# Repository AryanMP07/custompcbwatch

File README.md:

# Custom PCB Smartwatch

A self-contained smartwatch built around an ESP32 microcontroller and a round color display — a first custom PCB project, scoped to be finishable by a beginner and demoable as a resume/portfolio piece.

## Status

- [ ] Breadboard prototype validated
- [ ] Schematic complete (KiCad)
- [ ] ERC clean
- [ ] PCB layout complete
- [ ] DRC clean
- [ ] Gerbers exported
- [ ] PCB ordered
- [ ] Components ordered
- [ ] Board assembled
- [ ] Power-on / bring-up passed
- [ ] Firmware complete

*(Update this checklist as the project progresses.)*

## Core features

- ESP32-WROOM-32 — WiFi, NTP time sync, runs the firmware
- GC9A01 1.28" round SPI display, 240x240 — analog watch face with drawn hands/ticks
- Weather via Open-Meteo, refreshed periodically, with icons
- Single button to cycle screens: time / weather / date / extra info
- LDR-based auto-dim at night
- Battery percentage via a voltage-divider on one ADC pin
- WS2812 ("NeoPixel") RGB status LED — notifications / charging / low battery
- Coin vibration motor (single NPN transistor + flyback diode) for alerts
- MCP73831 LiPo charger IC + USB-C power input

## Repo structure

- KiCad project files (schematic, PCB, footprints, libraries) live at the repo root.
- `.gitignore` excludes KiCad backup/cache/autosave files, netlists, and exported BOM files — see that file for the full list.

## Collaboration workflow

KiCad's `.kicad_sch` / `.kicad_pcb` files don't diff or merge cleanly like code, so two people editing the same file at once causes painful conflicts. Rule of thumb:

1. `git pull` before opening KiCad.
2. Let the other person know you're working on the schematic/PCB.
3. Close KiCad, then `git add -A && git commit -m "..." && git push`.
4. Tell the other person when you're done so they can pull.

## Bill of materials (summary)

ESP32-WROOM-32 · GC9A01 240x240 round SPI display · MCP73831T-2ACI/OT LiPo charger · USB-C power-only connector · 3.7V 500mAh LiPo (JST-PH, protected) · SMD tactile button · LDR + divider resistor · WS2812 RGB LED · coin vibration motor + NPN transistor + flyback diode + base resistor · AMS1117-3.3 regulator (if needed) · 0603/0805 resistor & capacitor kits · programming header.

## Build sequence

1. Learn the basics (voltage/current, resistors/capacitors, SPI/I2C).
2. Breadboard prototype using dev boards (ESP32 dev board + GC9A01 breakout) to validate the concept.
3. KiCad: schematic → ERC → footprints/layout → DRC → Gerbers.
4. Order the bare PCB and all components (matching footprints exactly).
5. Solder the board; verify voltages with a multimeter before connecting the battery.
6. Bring up subsystems one at a time: LED blink → display → WiFi → vibration motor.
7. Write and flash firmware: WiFi + NTP → weather API → watch-face rendering → button screen-cycling → auto-dim → RGB LED status → vibration alerts.

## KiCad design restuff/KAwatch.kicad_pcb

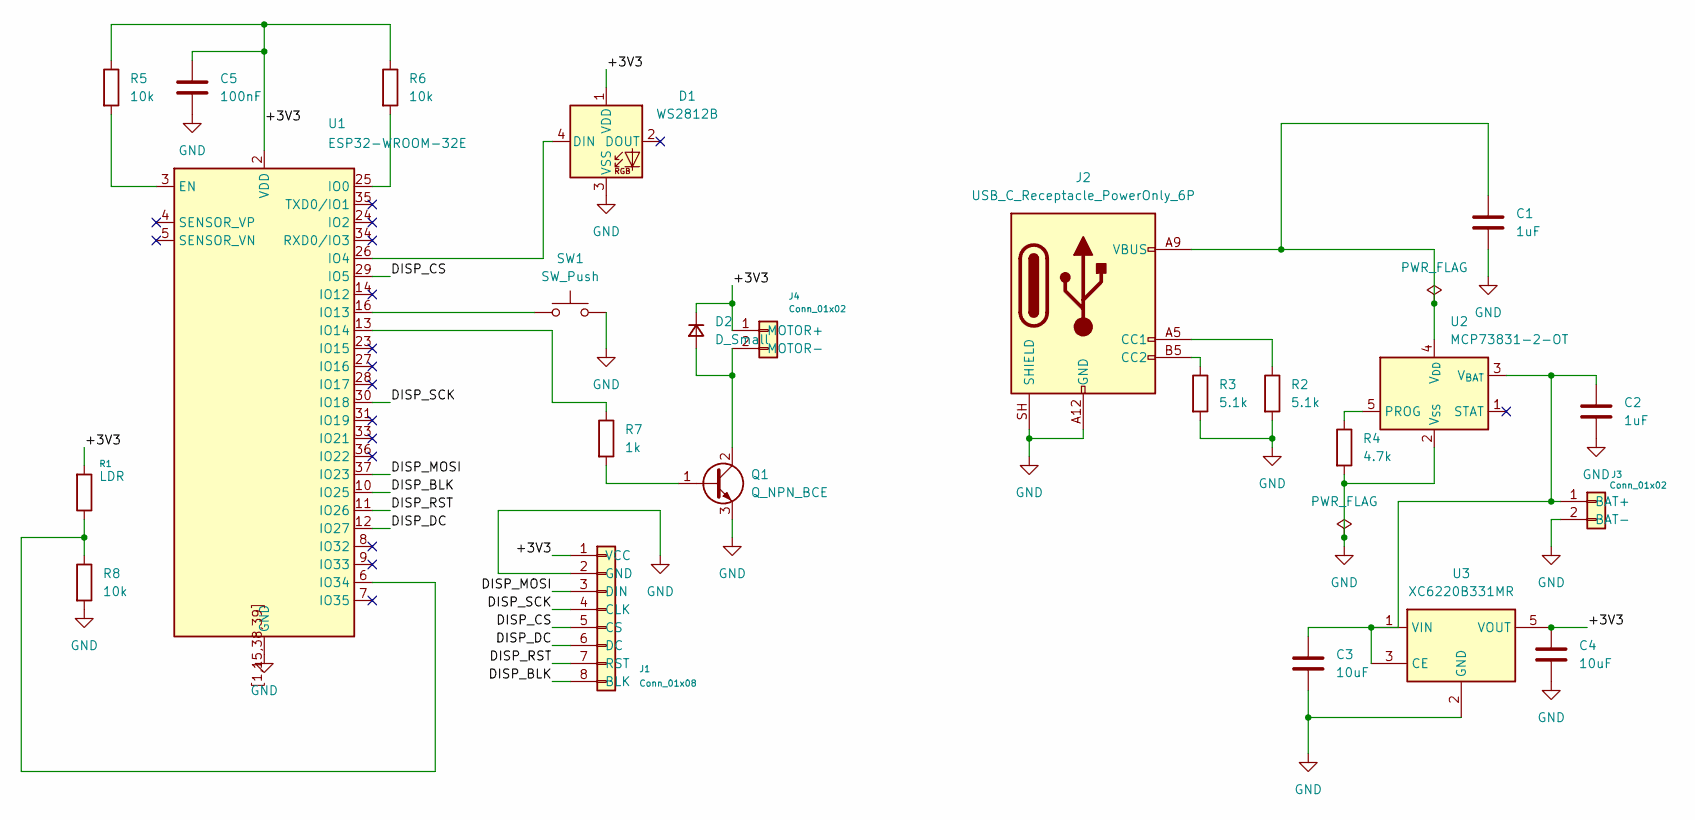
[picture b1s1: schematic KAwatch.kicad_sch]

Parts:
C1, C2: 1uF; C_0603_1608Metric
C3, C4: 10uF; C_0603_1608Metric
C5: 100nF; C_0603_1608Metric
D1: WS2812B; LED_WS2812B_PLCC4_5.0x5.0mm_P3.2mm
D2: D_Small; D_SOD-123
J1: Conn_01x08; PinHeader_1x08_P2.54mm_Vertical
J2: USB_C_Receptacle_PowerOnly_6P; USB_C_Receptacle_GCT_USB4125-xx-x_6P_TopMnt_Horizontal
J3: Conn_01x02; JST_PH_S2B-PH-K_1x02_P2.00mm_Horizontal
J4: Conn_01x02; PinHeader_1x02_P2.54mm_Vertical
Q1: Q_NPN_BCE; SOT-23
R1: LDR; R_0603_1608Metric
R2, R3: 5.1k; R_0603_1608Metric
R4: 4.7k; R_0603_1608Metric
R5, R6, R8: 10k; R_0603_1608Metric
R7: 1k; R_0603_1608Metric
SW1: SW_Push; SW_SPST_TL3342
U1: ESP32-WROOM-32E
U2: MCP73831-2-OT; SOT-23-5
U3: XC6220B331MR; SOT-23-5

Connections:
/+3V3: C4.1, C5.1, D1.1 (VDD), D2.1 (K), J1.1 (VCC), J4.1 (MOTOR+), R1.1, R5.1, R6.1, U1.2 (VDD), U3.5 (VOUT)
/DISP_BLK: J1.8 (BLK), U1.10 (IO25)
/DISP_CS: J1.5 (CS), U1.29 (IO5)
/DISP_DC: J1.6 (DC), U1.12 (IO27)
/DISP_MOSI: J1.3 (DIN), U1.37 (IO23)
/DISP_RST: J1.7 (RST), U1.11 (IO26)
/DISP_SCK: J1.4 (CLK), U1.30 (IO18)
GND: C1.2, C2.2, C3.2, C4.2, C5.2, D1.3 (VSS), J1.2 (GND), J2.A12 (GND), J2.B12 (GND), J2.SH (SHIELD), J3.2 (BAT-), Q1.3 (E), R2.2, R3.2, R4.2, R8.2, SW1.2, U1.1 (GND), U1.15 (GND), U1.38 (GND), U1.39 (GND), U1.[1,15,38,39] (GND), U2.2 (V_{SS}), U3.2 (GND)
unnamed: D1.4 (DIN), U1.26 (IO4)
unnamed: D2.2 (A), J4.2 (MOTOR-), Q1.2 (C)
unnamed: J2.A5 (CC1), R2.1
unnamed: J2.B5 (CC2), R3.1
unnamed: C2.1, C3.1, J3.1 (BAT+), U2.3 (V_{BAT}), U3.1 (VIN), U3.3 (CE)
unnamed: Q1.1 (B), R7.2
unnamed: R5.2, U1.3 (EN)
unnamed: R6.2, U1.25 (IO0)
unnamed: SW1.1, U1.16 (IO13)
unnamed: R7.1, U1.13 (IO14)
unnamed: R1.2, R8.1, U1.6 (IO34)
unnamed: R4.1, U2.5 (PROG)
unnamed: C1.1, J2.A9 (VBUS), J2.B9 (VBUS), U2.4 (V_{DD})

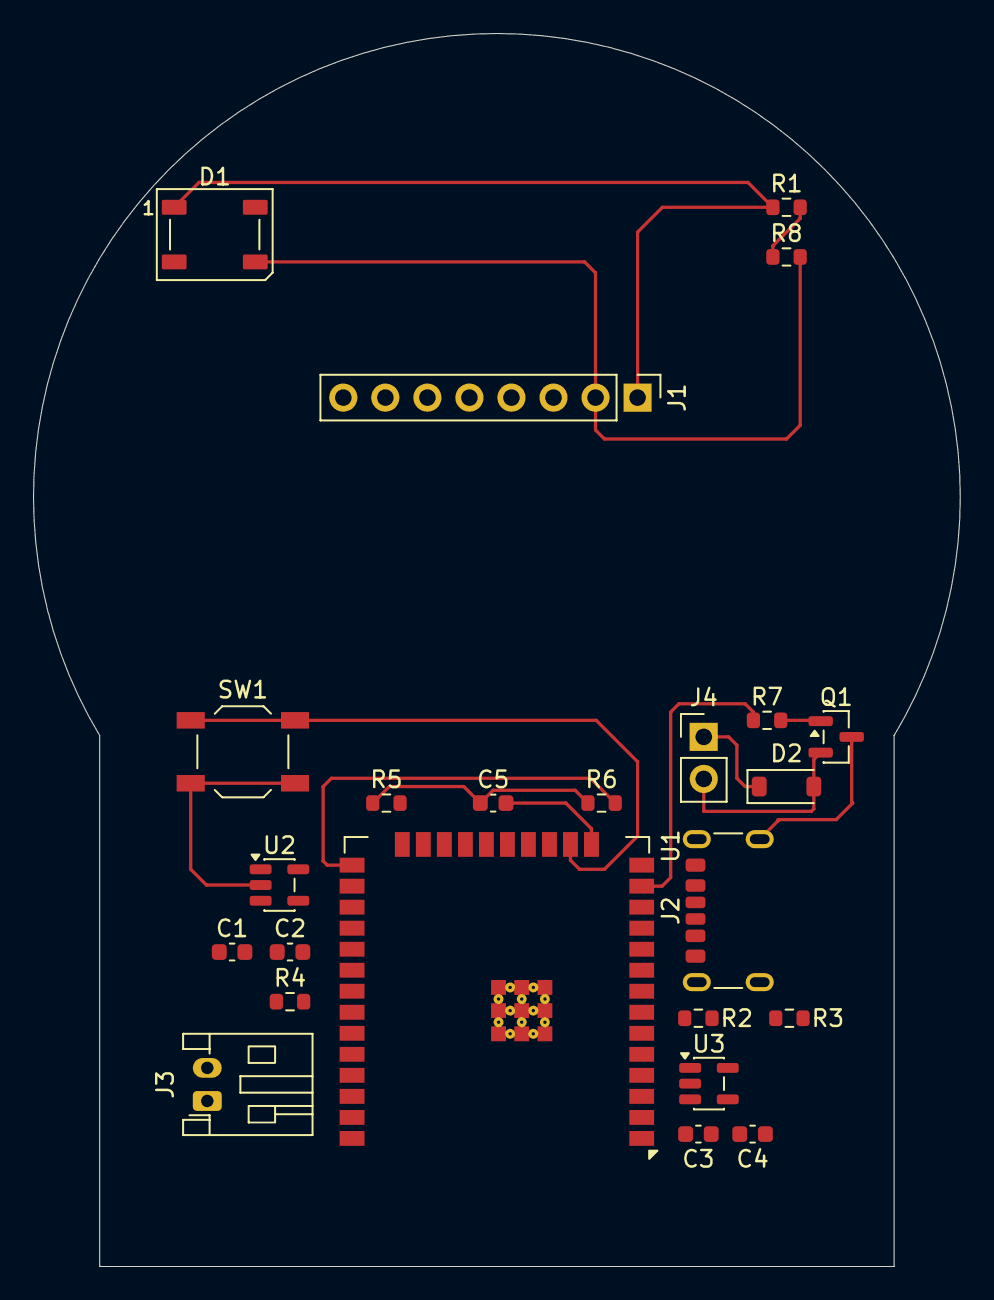
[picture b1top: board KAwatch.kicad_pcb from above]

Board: 2 copper layers, 56.0 x 74.5 mm, 24 parts (0 on the bottom side), 21 nets.
